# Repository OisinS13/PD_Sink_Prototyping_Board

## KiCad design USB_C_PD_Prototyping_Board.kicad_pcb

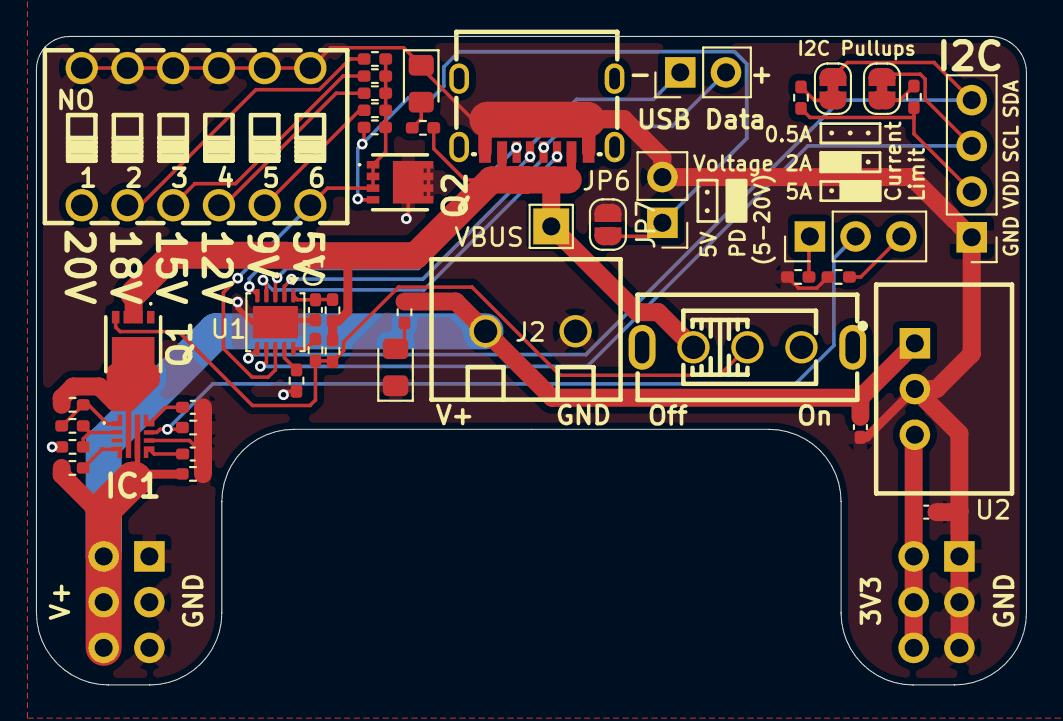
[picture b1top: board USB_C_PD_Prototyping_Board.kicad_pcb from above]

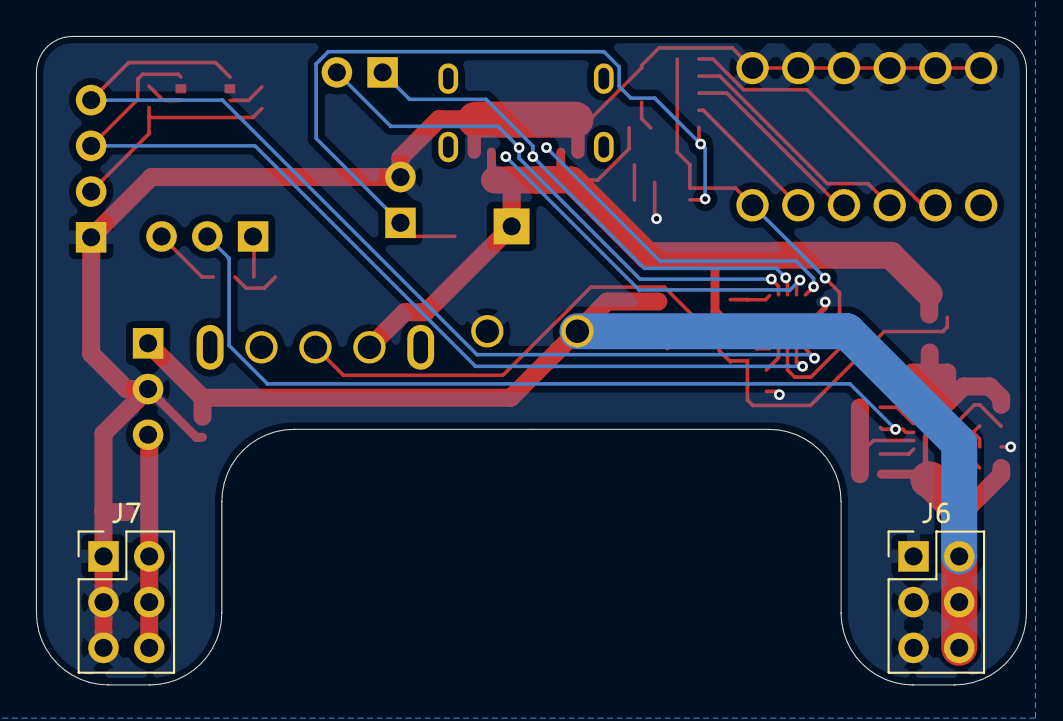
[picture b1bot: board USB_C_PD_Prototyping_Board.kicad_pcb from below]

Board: 2 copper layers, 55.0 x 36.0 mm, 47 parts (2 on the bottom side), 34 nets.

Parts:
C1, C7: 10uF; C_0402_1005Metric_Pad0.74x0.62mm_HandSolder
C5, C6: 220 pF; C_0402_1005Metric_Pad0.74x0.62mm_HandSolder
C8: 22uF; C_0402_1005Metric_Pad0.74x0.62mm_HandSolder
D1, D2: KT-0805G; LED_0805_2012Metric_Pad1.15x1.40mm_HandSolder
DIP1: DIPSWITCH_6PIN; SW-TH_DSWB06LHGET
IC1: TPS259474LRPWR
J1: USB_C_Receptacle; USB-TYPE-C-SMD_MC-403L68-Z10
J2: Power_out; CONN-TH_2P-P5.00_MX126-5.0-GN01-02P-CU-S-A
J3: Data_out; PinHeader_1x02_P2.54mm_Vertical
J5: Conn_01x04_Pin; PinHeader_1x04_P2.54mm_Vertical
J6, J7: Conn_02x02_Counter_Clockwise; PinHeader_2x03_P2.54mm_Vertical
JP1, JP4: SolderJumper_2_Bridged; SolderJumper-2_P1.3mm_Bridged_RoundedPad1.0x1.5mm
JP5: Jumper_2_Open; PinHeader_1x03_P2.54mm_Vertical
JP6: Jumper_2_Open; PinHeader_1x02_P2.54mm_Vertical
JP7: SolderJumper_2_Open; SolderJumper-2_P1.3mm_Open_RoundedPad1.0x1.5mm
Q1, Q2: DMP3018SFV-7; DMP3036SFV7
R1: 6K; R_0402_1005Metric_Pad0.72x0.64mm_HandSolder
R2, R18, R19: 10K; R_0402_1005Metric_Pad0.72x0.64mm_HandSolder
R3: 14K; R_0402_1005Metric_Pad0.72x0.64mm_HandSolder
R4, R8, R17: 18K; R_0402_1005Metric_Pad0.72x0.64mm_HandSolder
R5: 10; R_0402_1005Metric_Pad0.72x0.64mm_HandSolder
R6: 5.1K; R_0402_1005Metric_Pad0.72x0.64mm_HandSolder
R7, R9: 49.9K; R_0402_1005Metric_Pad0.72x0.64mm_HandSolder
R10: 200K; R_0402_1005Metric_Pad0.72x0.64mm_HandSolder
R11: 750K; R_0402_1005Metric_Pad0.72x0.64mm_HandSolder
R12: 50K; R_0402_1005Metric_Pad0.72x0.64mm_HandSolder
R13: 6.49K; R_0402_1005Metric_Pad0.72x0.64mm_HandSolder
R14: 700; R_0402_1005Metric_Pad0.72x0.64mm_HandSolder
R15: 47K; R_0402_1005Metric_Pad0.72x0.64mm_HandSolder
R16: 15K; R_0402_1005Metric_Pad0.72x0.64mm_HandSolder
R20: 2K2; R_0402_1005Metric_Pad0.72x0.64mm_HandSolder
R21: 22K; R_0402_1005Metric_Pad0.72x0.64mm_HandSolder
SW1: Power_out_switch; SW-TH_SS-12F44-G5_C2998807
TP2: TESTPOINTROUND1.5MMNO; TestPoint_THTPad_2.0x2.0mm_Drill1.0mm
U1: HUSB238_xxxDD; WDFN-10-1EP_3x3mm_P0.5mm_EP1.8x2.5mm
U2: K7803-500R3_C909766; PWRM-TH_K78XX-500R3

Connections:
+3V3: C8.2, J7.2, J7.4, J7.6, U2.3 (+Vo)
/DVDT: C6.2, IC1.7 (DVDT_1), IC1.13 (DVDT_2)
/I_TIMER: C5.2, IC1.10 (ITIMER_1), IC1.14 (ITIMER_2)
/PGTH: IC1.4 (PGTH/~FLT_1), IC1.12 (PGTH/~FLT_2), R15.1
/UVLO: IC1.1 (EN/UVLO_1), IC1.11 (EN/UVLO_2), R10.1, R11.1
CC1: J1.A5 (CC1), U1.4 (CC1)
CC2: J1.B5 (CC2), U1.5 (CC2)
D+: J1.A6 (D+), J3.2, U1.2 (D+)
D-: J1.A7 (D-), J3.1, U1.3 (D-)
GND: C1.1, C5.1, C6.1, C7.1, C8.1, D1.1 (K), D2.1 (K), DIP1.1, DIP1.2, DIP1.3, DIP1.4, DIP1.5, DIP1.6, IC1.8 (GND), J1.B1 (GND), J1.B12 (GND), J2.2, J5.1, J6.1, J6.3, J6.5, J7.1, J7.3, J7.5, JP6.2 (B), JP7.2 (B), Q2.5, R12.1, R13.1, R14.2, R16.2, R20.2, R21.1, U1.11 (GND), U2.2 (GND)
unnamed: D1.2 (A), R8.1
unnamed: D2.2 (A), R17.1
unnamed: DIP1.8, R4.1
unnamed: DIP1.9, R3.1
unnamed: DIP1.10, R2.1
unnamed: DIP1.11, R1.1
unnamed: IC1.9 (ILM), JP5.2 (C), R13.2
unnamed: IC1.2 (OVLO/_OVCSEL), R11.2, R12.2
unnamed: JP1.2 (B), R19.1
unnamed: JP4.2 (B), R18.1
unnamed: JP5.1 (A), R20.1
unnamed: JP5.3 (B), R14.1
unnamed: JP6.1 (A), JP7.1 (A), Q2.4 (G), R9.1
unnamed: Q1.4 (G), R6.1, R7.2, SW1.2 (B)
unnamed: R6.2, U1.10 (GATE)
unnamed: R21.2, U1.9 (ISET)
unnamed: C1.2, R5.2, U1.1 (VIN)
unnamed: DIP1.12, Q2.1 (S), Q2.2 (S), Q2.3 (S), R1.2, R2.2, R3.2, R4.2, R9.2, U1.8 (VSET)
SCL: J5.3, JP4.1 (A), U1.7 (SCL)
SDA: J5.4, JP1.1 (A), U1.6 (SDA)
VBUS: J1.B4 (VBUS), J1.B9 (VBUS), Q1.2 (S), Q1.3 (S), R5.1, R7.1, R8.2, SW1.1 (A), TP2.1 (1_1)
VDD: J5.2, R18.2, R19.2
VFuse: IC1.5 (IN), Q1.5, R10.2
VOUT: C7.2, IC1.6 (OUT), J2.1, J6.2, J6.4, J6.6, R15.2, R16.1, R17.2, U2.1 (Vin)

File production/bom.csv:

Designator,Footprint,Quantity,Value,LCSC Part #
C1,402,1,10uF,
"C5, C6",402,2,220 pF,
"C7, C8",402,2,4.7uF,
"D1, D2",805,2,KT-0805G,
DIP1,SW-TH_DSWB06LHGET,1,DIPSWITCH_6PIN,C99416
IC1,TPS259474LRPWR,1,TPS259474LRPWR,
IC2,TO-252-2,1,BD33FC0FP-E2,
J1,USB-TYPE-C-SMD_MC-403L68-Z10,1,USB_C_Receptacle,C47326496
J2,CONN-TH_2P-P5.00_MX126-5.0-GN01-02P-CU-S-A,1,Power_out,C5188434
J3,PinHeader_1x02_P2.54mm_Vertical,1,Data_out,
J5,PinHeader_1x04_P2.54mm_Vertical,1,Conn_01x04_Pin,
"J6, J7",PinHeader_2x03_P2.54mm_Vertical,2,Conn_02x02_Counter_Clockwise,
JP6,PinHeader_1x02_P2.54mm_Vertical,1,Jumper_2_Open,
JP5,PinHeader_1x03_P2.54mm_Vertical,1,Jumper_3_Open,
"Q1, Q2",DMP3036SFV7,2,DMP3018SFV-7,
R1,402,1,6K,
R10,402,1,200k,
R11,402,1,750k,
R12,402,1,50k,
R13,402,1,6.49k,
R14,402,1,700,
R15,402,1,47k,
R16,402,1,15k,
"R17, R8",402,2,9K1,
"R18, R19, R2",402,3,10K,
R20,402,1,2.2k,
R3,402,1,14K,
R4,402,1,18K,
R5,402,1,10,
R6,402,1,5.1k,
"R7, R9",402,2,49.9k,
SW1,SW-TH_SS-12F44-G5_C2998807,1,Power_out_switch,C2998807
"TP1, TP2, TP3",TestPoint_THTPad_2.0x2.0mm_Drill1.0mm,3,TESTPOINTROUND1.5MMNO,
U1,WDFN-10-1EP_3x3mm_P0.5mm_EP1.8x2.5mm,1,HUSB238_xxxDD,
